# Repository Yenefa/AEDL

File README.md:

# AEDL

**Autonomous Engineering Design Loop · 自主嵌入式工程研发闭环**

AEDL 探索如何在明确的人类审批边界内，把自然语言需求转化为可审计的嵌入式设计候选，并让需求合同、EDA 产物、固件、验证器和 Evidence 保持可追溯。

**北极星**：AEDL 的最终目标是**在受控工程流程下正确交付实体板卡**——从自然语言需求出发，经过可审计的设计闭环，产出能一次做对、可追溯的硬件。直接生成 PCB 不难，难的是让结果可信：M2 载板在终检时暴露的六项硬件语义缺陷（USB D+/D- 接反、SHT30 ADDR 悬空等，PIT-20260830-001）证明，生成器自证与文件一致性无法保证正确性。因此 AEDL 把“做板子”工程化为可验证闭环，并以 **EDD-001** 作为第一块在 Sandbox 验证下设计的兑现板。

本仓库是 AEDL 的**集成与技术主张真源**。当前已经具备确定性合同、失败关闭门禁、候选/证据隔离、M2 硬件载体和软件验证基线；它仍不是一个已经完成、可以无人监督下单的通用硬件 Agent。

## Human-directed, AI-assisted · 人类主导，AI 辅助

AEDL is human-directed and AI-assisted.
The project owner defines product scope, acceptance criteria, architecture boundaries, verification policy, engineering claims, and release decisions.
AI agents are used for research, implementation, testing, documentation, and adversarial review.

AEDL 由人类主导、AI 辅助：项目负责人定义产品范围、验收标准、架构边界、验证政策、工程主张与发布决策；AI Agent 承担研究、实现、测试、文档与对抗性审查。

| Area | Owner |
| --- | --- |
| Product direction | Yenefa |
| Scope / acceptance criteria | Yenefa |
| Architecture approval | Yenefa |
| Verification policy | Yenefa + Percy (SHARED) |
| Engineering claims | Yenefa |
| Final merge / release | Human review + human merge; release sign-off: Yenefa |
| Implementation assistance | AI-assisted |
| Testing / adversarial review | AI-assisted |
| Documentation assistance | AI-assisted |

> Ownership here means **decision and approval authority, not sole authorship**. Implementation, research, tests and documentation in this repository are routinely AI-assisted, and every AI contribution stays on the record.
> 这里的 Owner 指**决策与批准权，不是"唯一作者"**；仓库的实现、研究、测试与文档普遍由 AI 协助完成，全部记录保留可追溯。
>
> 逐条职责与证据：[Human Ownership](docs/HUMAN_OWNERSHIP.md) · 归因分类与红线：[Attribution Policy](docs/compliance/ATTRIBUTION_POLICY.md) · AI 使用聚合视图：[AI Usage Summary](docs/compliance/AI_USAGE_SUMMARY.md)。

## 当前真实状态

> README 只描述稳定边界，不复制会过期的门禁计数。每次接手请以 [HANDOFF](docs/HANDOFF.md)、[Evidence Index](docs/evidence/EVIDENCE_INDEX.md) 和当前结构化门禁结果为准。

| 范围 | 当前边界 | 权威入口 |
| --- | --- | --- |
| M2 ESP32-C3/SHT30 设计 | 已有原理图、PCB、制造导出物和机器/静态验证记录；**物理线已冻结（2026-09-01 裁决：不再下单/重签/换料）**，其验证机制保留为 Sandbox 地基 | [M2 硬件目录](src/hardware/m2-board/)、[HANDOFF](docs/HANDOFF.md) |
| 制造放行 | **BLOCKED**；`manufacturing_release=false`，尚未重新人工签发，不得据旧记录下单 | [board_review_v1.json](gates/board_review_v1.json) |
| 数据手册合同 | 仍有人工签发项；自动检查不能替代具名工程复核 | [硬件 Evidence](src/hardware/m2-board/evidence/)、[HANDOFF](docs/HANDOFF.md) |
| 实体板验证 | **NOT_RUN**；上电、功耗、BLE、传感器精度、USB 眼图、瞬态与长期稳定性仍待回件 | [Evidence Index](docs/evidence/EVIDENCE_INDEX.md) |
| EDD-001 自主设计闭环 | Sandbox 运行时已实现；真实 preflight 对缺失资料、POWER 合同、compiler 和独立 verifier 保持失败关闭 | [Sandbox 设计规格](docs/superpowers/specs/2026-09-01-edd001-engineering-design-sandbox-design.md)、[HANDOFF](docs/HANDOFF.md) |

没有当前 Evidence 支撑的性能、可制造性或自主能力，不应从历史 PASS、文件存在或工具清单中推导。

## 系统边界

```text
自然语言需求
  → 可签发需求合同
  → 受约束的设计候选
  → EDA / firmware compiler
  → 独立 read-back verifier
  → content-addressed Evidence
  → 人工 Review / 晋升 / 制造决策
```

核心原则：

- **失败关闭**：`UNKNOWN`、缺资料或证据失配不能降级为 PASS。
- **候选不污染基线**：设计变更先进入 candidate，冻结 baseline 不原地改写。
- **验证器独立**：生成器自报成功不能代替独立解析与对抗性验证。
- **人机权限分离**：Agent 可以生成、诊断和验证；人工保留候选晋升、制造签发、下单和最终 Review。
- **证据分级**：静态检查、仿真、软件 loopback 与实体硬件结果分别记录，不能互相冒充。

## 从这里开始

### 推荐阅读顺序

```text
README.md
  ↓  docs/HUMAN_OWNERSHIP.md                    人类职责、决策权与验收权
  ↓  docs/compliance/DECISIONS.md               架构与治理决策（ADR）
  ↓  技术文档（HANDOFF / COLLABORATION / CONTROL_PLANE / Evidence）
  ↓  docs/compliance/AI_USAGE_SUMMARY.md        AI 使用的工作单元聚合视图
  ↓  docs/compliance/AI_USAGE_LOG.md            完整可审计索引（逐条真源在 ai-usage/）
```

AI 台账是**审计层**，不是入门读物：先看清"谁做决策、谁验收"，再看 AI 如何协助。

### 人类开发者

1. 阅读 [HANDOFF](docs/HANDOFF.md) 获取最新分支、阻塞项和验证状态。
2. 阅读 [协作协议](docs/COLLABORATION.md)，从当前协作基线创建 Issue 对应的任务分支。
3. 一个 Issue 只设一个 Owner 和一组独占写路径；通过 Draft PR 交接给另一名真人 Review。

不要仅凭 GitHub 默认分支名判断当前完整工作线；协作基线以 HANDOFF 为准。

### AI Agent

新会话 / 新 clone 先读根目录 [AGENT_ONBOARDING.md](AGENT_ONBOARDING.md)：环境自检（autocrlf /
Python 3.9 / uv / gh）、AECP 生命周期速查与红线。然后，在产生任何实质贡献前，必须依次完整读取：

1. 根目录 [AGENTS.md](AGENTS.md)；
2. [docs/HANDOFF.md](docs/HANDOFF.md)；
3. [docs/COLLABORATION.md](docs/COLLABORATION.md)；
4. 当前 Issue / PR 的 Goal、Scope、Owned paths 和 Acceptance Criteria。

硬件发布、BOM、原理图、PCB 或制造任务还必须读取 [PROJECT_PITFALLS](docs/knowledge/PROJECT_PITFALLS.md) 与 [IMPROVEMENT_SYSTEM](docs/knowledge/IMPROVEMENT_SYSTEM.md)。

## 安全验证入口

以下命令不会被 README 宣称为实体硬件验证：

```powershell
# 主仓库确定性单元/集成测试
py -3 -S -m unittest discover -s tests

# Sandbox 运行时测试
uv run --frozen --project sandbox_runtime python -m unittest discover -s sandbox_runtime/tests -p "test_*.py"

# 真实 EDD-001 preflight；存在资料/覆盖缺口时应返回 BLOCKED
uv run --frozen --project sandbox_runtime python -m aedl_sandbox.cli preflight --repo-root . --domain EDD-001
```

完整 M2 runner 会刷新 `notes/m2-evidence-reset/` 下的运行证据。只有在 Issue 明确拥有 Evidence 写路径、已保存旧批次并准备记录新运行时，才执行：

```powershell
py -3 gates\run_gates.py
```

不得为了得到绿色输出，在普通文档或协作任务中原地重跑并覆盖证据。

## 双仓库结构

| 仓库 | 责任 | 不承担的责任 |
| --- | --- | --- |
| [`Yenefa/AEDL`](https://github.com/Yenefa/AEDL) | 集成代码、工程合同、ADR、合规台账、比赛主张与正式 Evidence 索引 | 不把未经晋升的实验结果直接包装成产品能力 |
| [`Yenefa/AEDL-spike`](https://github.com/Yenefa/AEDL-spike) | 协议执行器实验、故障注入样例和过程 Evidence 卫星 | 不单独决定主仓架构、制造放行或比赛技术主张 |

卫星成果回流主仓时，必须引用精确 spike commit、文件路径、限制和复现方法，并通过主仓 Issue 与另一名真人 Review 的 PR。当前卫星治理见 [`AEDL-spike` Draft PR #2](https://github.com/Yenefa/AEDL-spike/pull/2)。

## 项目结构

| 路径 | 内容 |
| --- | --- |
| `src/hardware/m2-board/` | M2 intent、KiCad 原理图/PCB、硬件 Evidence 合同 |
| `src/firmware/` | 固件源码 |
| `gates/` | 失败关闭门禁、合同与制造放行真源 |
| `sandbox_runtime/` | Design / Execution / Trust 三层 Sandbox 运行时 |
| `tests/` | 主仓库确定性测试与对抗性夹具 |
| `notes/` | 机器生成的运行批次、manifest 与原始证据 |
| `delivery/` | 当前制造导出物；存在不等于获准下单 |
| `docs/evidence/` | 可验证主张与原始证据索引 |
| `docs/compliance/` | AI 使用、第三方资源、ADR 与贡献边界 |
| `docs/competition/` | 融合图、开放成果和提交检查资产 |
| `web/` | 需求澄清工作台 |
| `tools/` | 建板、布线、导出、评审和文档工具 |

## 协作与审计

标准路径是：

```text
Issue → task branch → exact-path staging → tests → Draft PR
      → another human review → merge decision
```

- 正式团队成员、AI 贡献和第三方资源分别登记，不能混写成“全部团队自研”。
- AI 的实质贡献按**可审计工作单元**逐条记录在 [docs/compliance/ai-usage/](docs/compliance/ai-usage/)；默认浏览入口是 [AI_USAGE_SUMMARY.md](docs/compliance/AI_USAGE_SUMMARY.md)（工作单元聚合），完整索引为 [AI_USAGE_LOG.md](docs/compliance/AI_USAGE_LOG.md)（脚本生成，禁手改）。审核状态保持 `PENDING_HUMAN_REVIEW`。
- 关键决策见 [DECISIONS](docs/compliance/DECISIONS.md)，第三方与许可证边界见 [THIRD_PARTY_RESOURCES](docs/compliance/THIRD_PARTY_RESOURCES.md)。
- 仓库当前的具体分支策略与 GitHub 强制能力边界见 [协作协议](docs/COLLABORATION.md)。

## 许可

AEDL 自研代码与文档按 [Apache License 2.0](LICENSE) 发布；第三方归因与再分发边界见 [NOTICE](NOTICE) 和 [THIRD_PARTY_RESOURCES](docs/compliance/THIRD_PARTY_RESOURCES.md)。冻结的数据手册、图纸和其他外部资料版权归各权利人，本仓库不将其声明为团队作品。

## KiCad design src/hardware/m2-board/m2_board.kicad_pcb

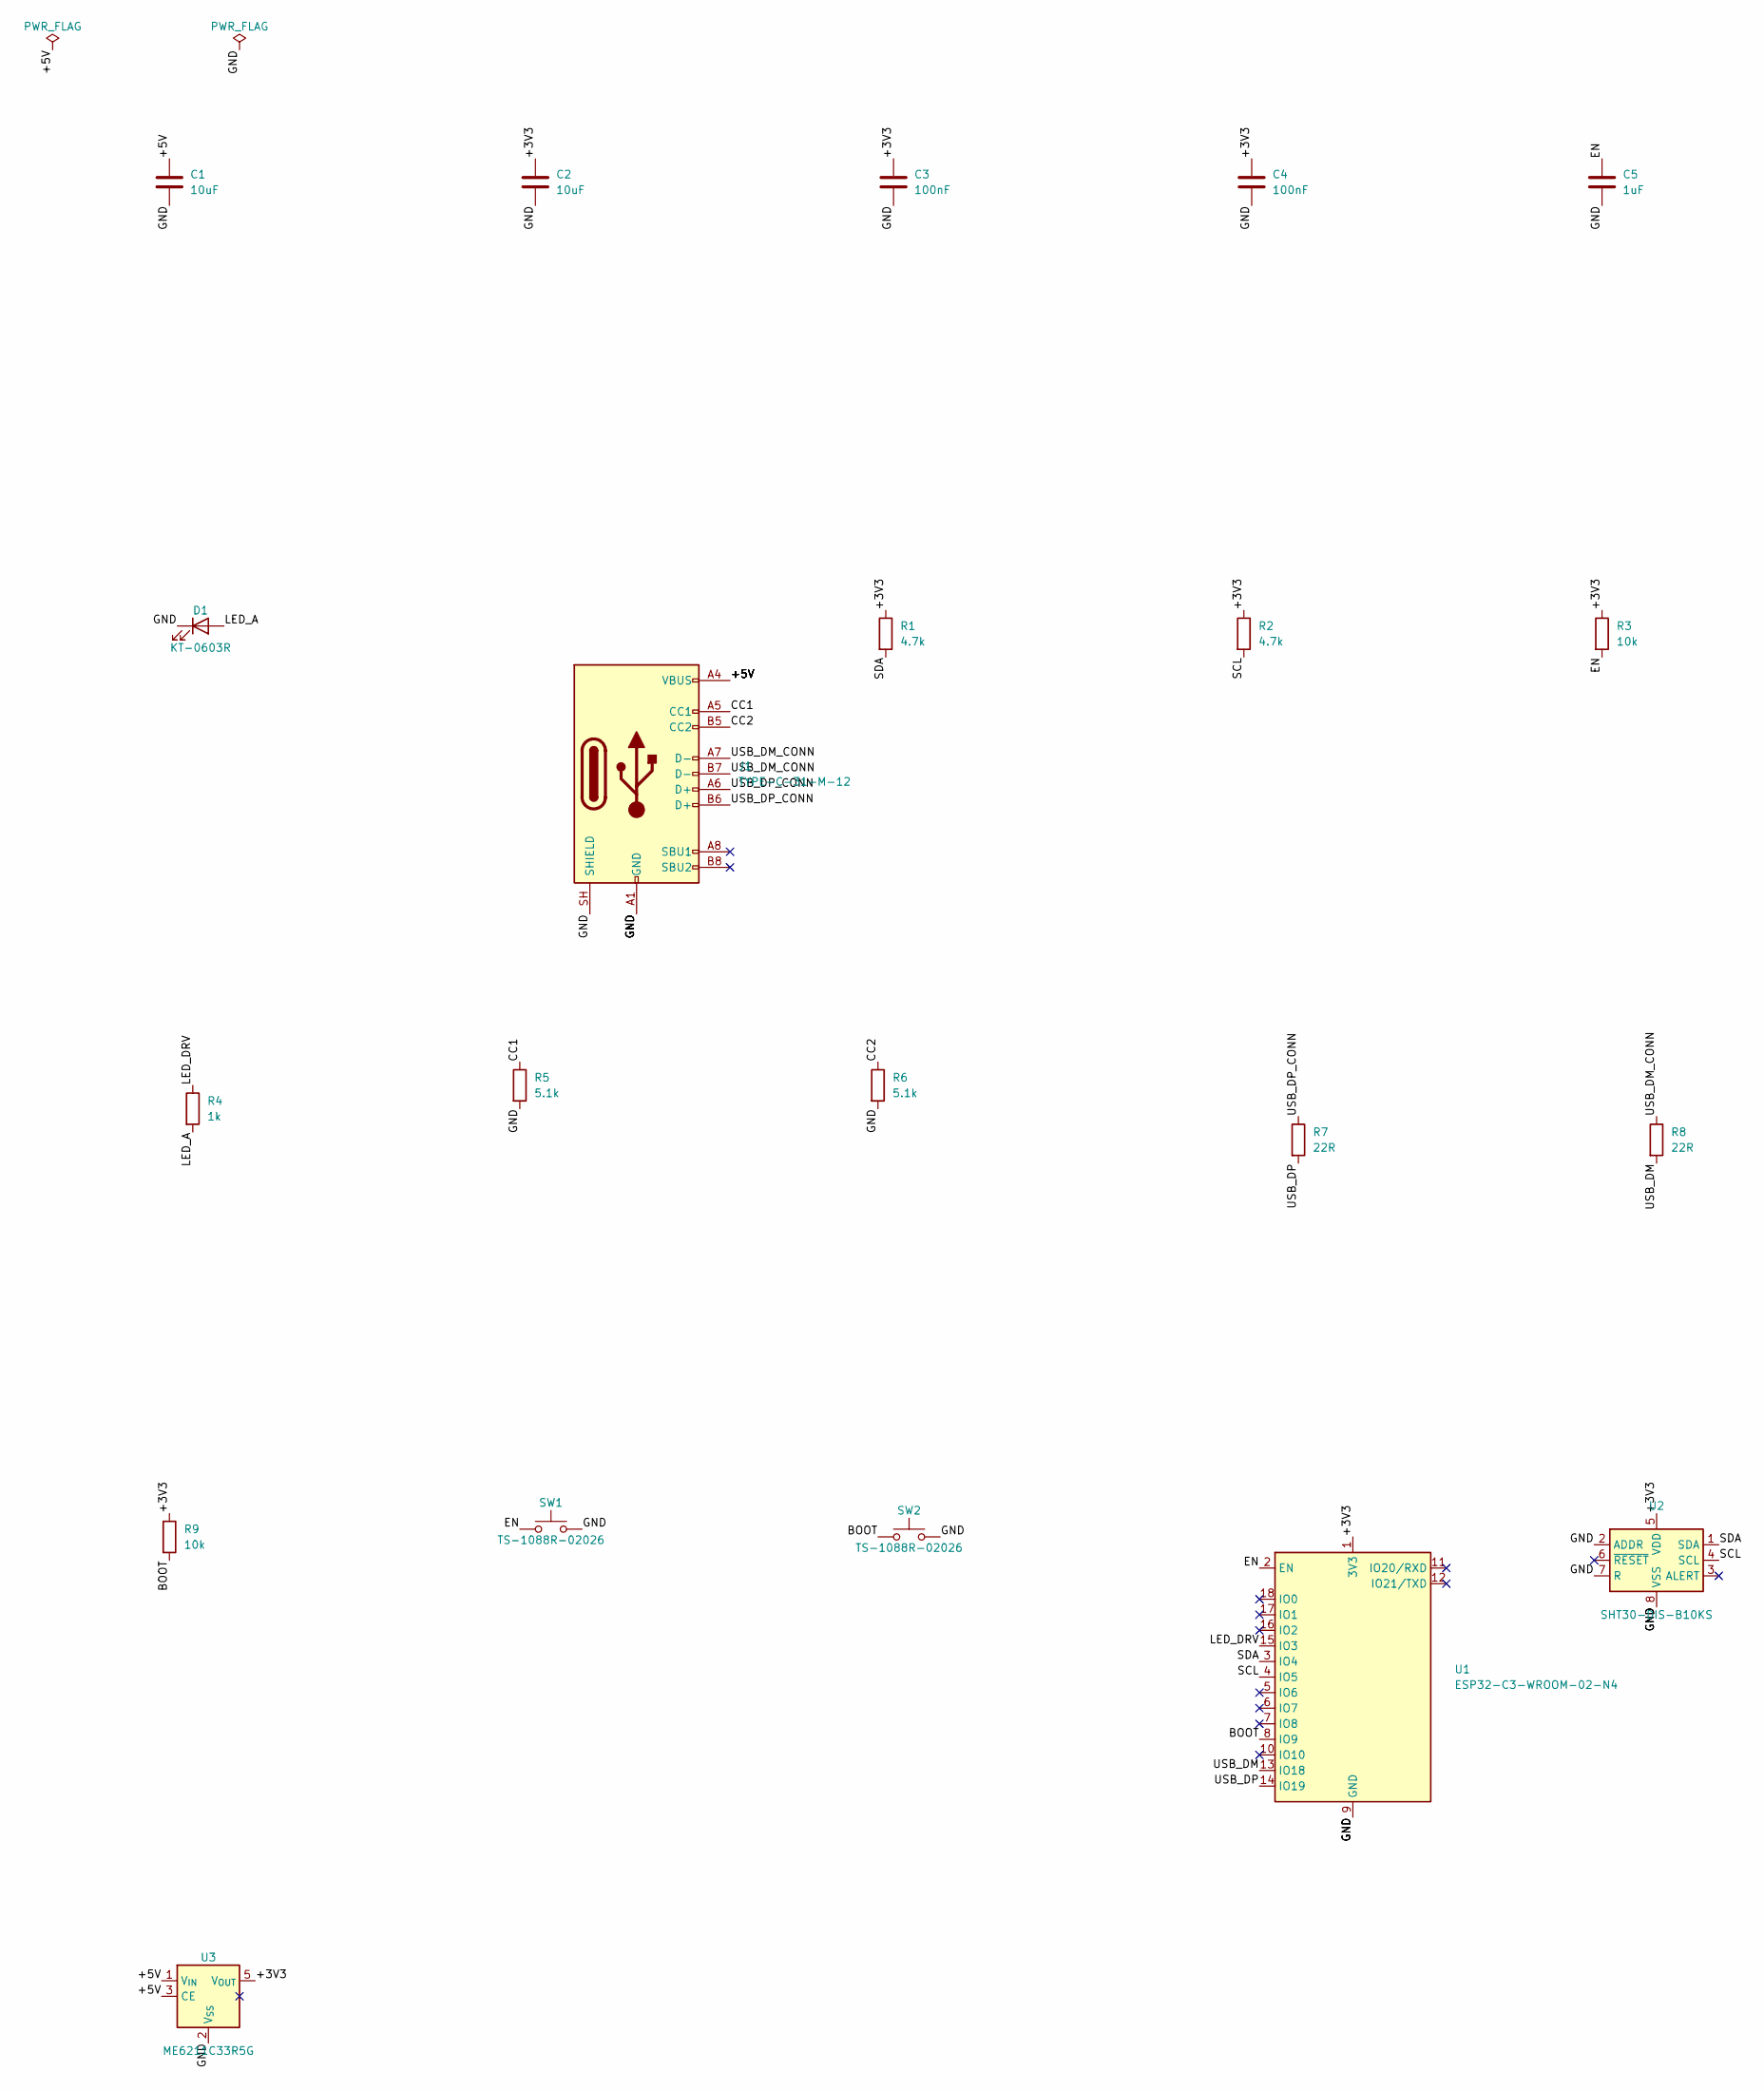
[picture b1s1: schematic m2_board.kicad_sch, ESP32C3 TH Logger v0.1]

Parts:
C1, C2: 10uF; C_0805_2012Metric
C3, C4: 100nF; C_0603_1608Metric
C5: 1uF; C_0603_1608Metric
D1: KT-0603R; LED_0603_1608Metric
J1: TYPE-C-31-M-12
R1, R2: 4.7k; R_0603_1608Metric
R3, R9: 10k; R_0603_1608Metric
R4: 1k; R_0603_1608Metric
R5, R6: 5.1k; R_0603_1608Metric
R7, R8: 22R; R_0603_1608Metric
SW1, SW2: TS-1088R-02026
U1: ESP32-C3-WROOM-02-N4
U2: SHT30-DIS-B10KS
U3: ME6211C33R5G; SOT-353

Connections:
+3V3: C2.1, C3.1, C4.1, R1.1, R2.1, R3.1, R9.1, U1.1 (3V3), U2.5 (VDD), U3.5 (V_{OUT})
+5V: C1.1, J1.A4 (VBUS), J1.A9 (VBUS), J1.B4 (VBUS), J1.B9 (VBUS), U3.1 (V_{IN}), U3.3 (CE)
BOOT: R9.2, SW2.1, U1.8 (IO9)
CC1: J1.A5 (CC1), R5.1
CC2: J1.B5 (CC2), R6.1
EN: C5.1, R3.2, SW1.1, U1.2 (EN)
GND: C1.2, C2.2, C3.2, C4.2, C5.2, D1.1 (K), J1.A1 (GND), J1.A12 (GND), J1.B1 (GND), J1.B12 (GND), J1.SH (SHIELD), R5.2, R6.2, SW1.2, SW2.2, U1.9 (GND), U1.19 (GND), U2.2 (ADDR), U2.7 (R), U2.8 (VSS), U2.9 (VSS), U3.2 (V_{SS})
LED_A: D1.2 (A), R4.2
LED_DRV: R4.1, U1.15 (IO3)
SCL: R2.2, U1.4 (IO5), U2.4 (SCL)
SDA: R1.2, U1.3 (IO4), U2.1 (SDA)
USB_DM: R8.2, U1.13 (IO18)
USB_DM_CONN: J1.A7 (D-), J1.B7 (D-), R8.1
USB_DP: R7.2, U1.14 (IO19)
USB_DP_CONN: J1.A6 (D+), J1.B6 (D+), R7.1

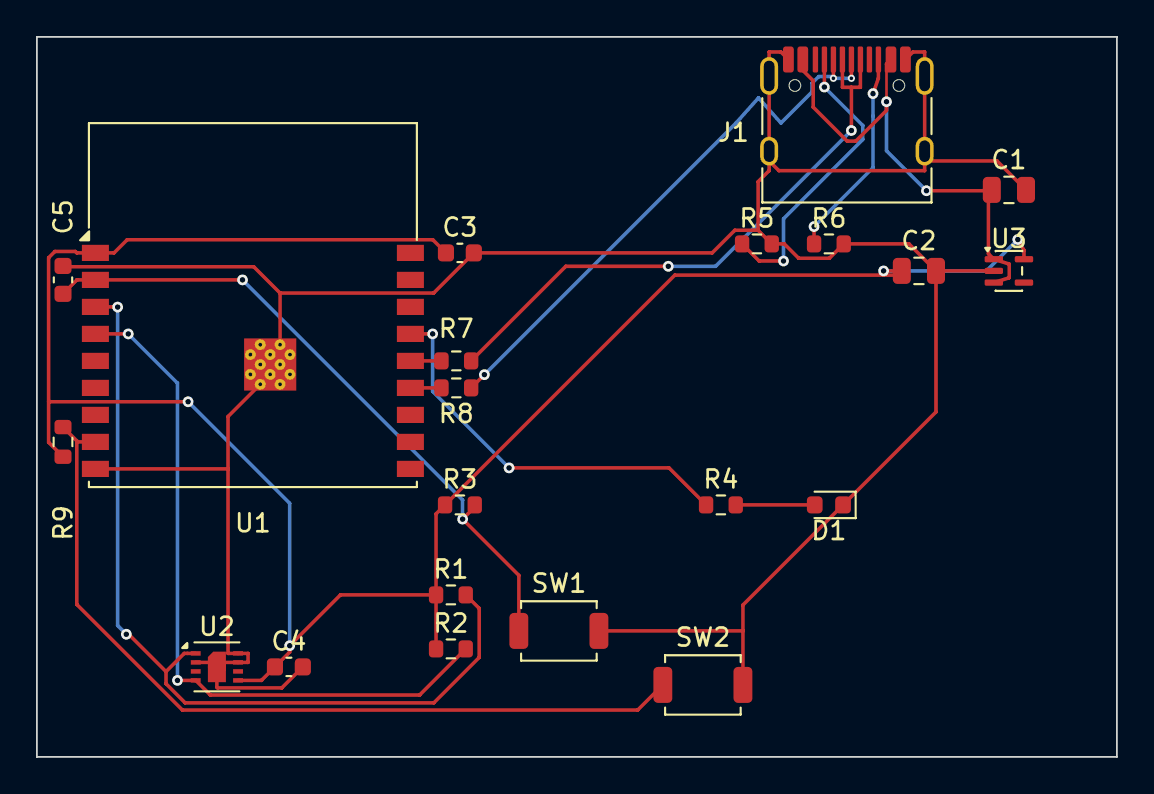
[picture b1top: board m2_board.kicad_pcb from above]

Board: 2 copper layers, 60.0 x 40.0 mm, 21 parts (0 on the bottom side), 15 nets.

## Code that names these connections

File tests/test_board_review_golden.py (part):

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
    def test_pins_map_keys_are_ref_dot_pad(self):
        pins = parsed_fixture()["pins"]
        self.assertEqual(pins["J1.A6"], "USB_DP_CONN")
        self.assertEqual(pins["U1.14"], "USB_DP")
        self.assertEqual(pins["R7.2"], "USB_DP")
        self.assertEqual(pins["C1.1"], "+3V3")
        self.assertEqual(pins["U3.VIN"], "+5V")

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
    def test_usb_routing_fails_when_a_pin_is_bound_to_the_wrong_net(self):
        pins = dict(self.pcb["pins"])
        pins["U1.14"] = "USB_DM"
        verdict = review_usb_routing(self.pcb["segments"], pins)
        self.assertEqual(verdict["status"], "fail")
        self.assertIn("U1.14", " ".join(verdict["measured"]["endpoint_mismatches"]))
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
